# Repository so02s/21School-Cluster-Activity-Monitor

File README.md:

# 21School-Cluster-Activity-Monitor
### Description
In order to visualize clusters computers accesibility for students and make finding a coding place for oneself easier, School 21's Lab Manager Freimor (Ricky in School 21) came up with the idea of autonomous Cluster Activity Monitor.
It should be set up on each of the School's floors. We've managed to set it up on the 2nd floor.
Monitor has a map embedded in its graphics. It lights up LEDs, showing which Mac seats are occupied, which are free to use and other types of seat status. It's connected to a local network and pulls data from the metrics data-point server. 
* Monitor shows seats that are either taken, free, covid-free or used for exam.
* It also lights up the viewer's position on the map.
* Brightness of the LED is dependant on ambient light level, due to embedded light sensor.
* It should potentially support extra add-ons.

### Monitor consists of:
* 5 front PCB's which we call "modules", with school claster names (Atrium, Illusion, Oasis, Atlantis and Mirage)
  * ~450 SK9822 2020 leds
  * STM32F030* microcontroller
* 1 "motherboard" PCB
  * Raspberry Pi Zero W
  * ADS1115 for photoresistor
* Mean Well IRM-60-5ST power supply
* 3D printed skeleton structure
  * M1.2 inserted nuts and bolts for fixing modules in 3d printed front layer
  * M4 inserted nuts and bolts for fixing front layer to skeleton main body
  * 4 wall plug for fixing main body to wall
* Front PCB's shield made of polycarbonate sheet

<details><summary>Photos</summary>

</details>

Done by team: Ricky, Bomanyte.

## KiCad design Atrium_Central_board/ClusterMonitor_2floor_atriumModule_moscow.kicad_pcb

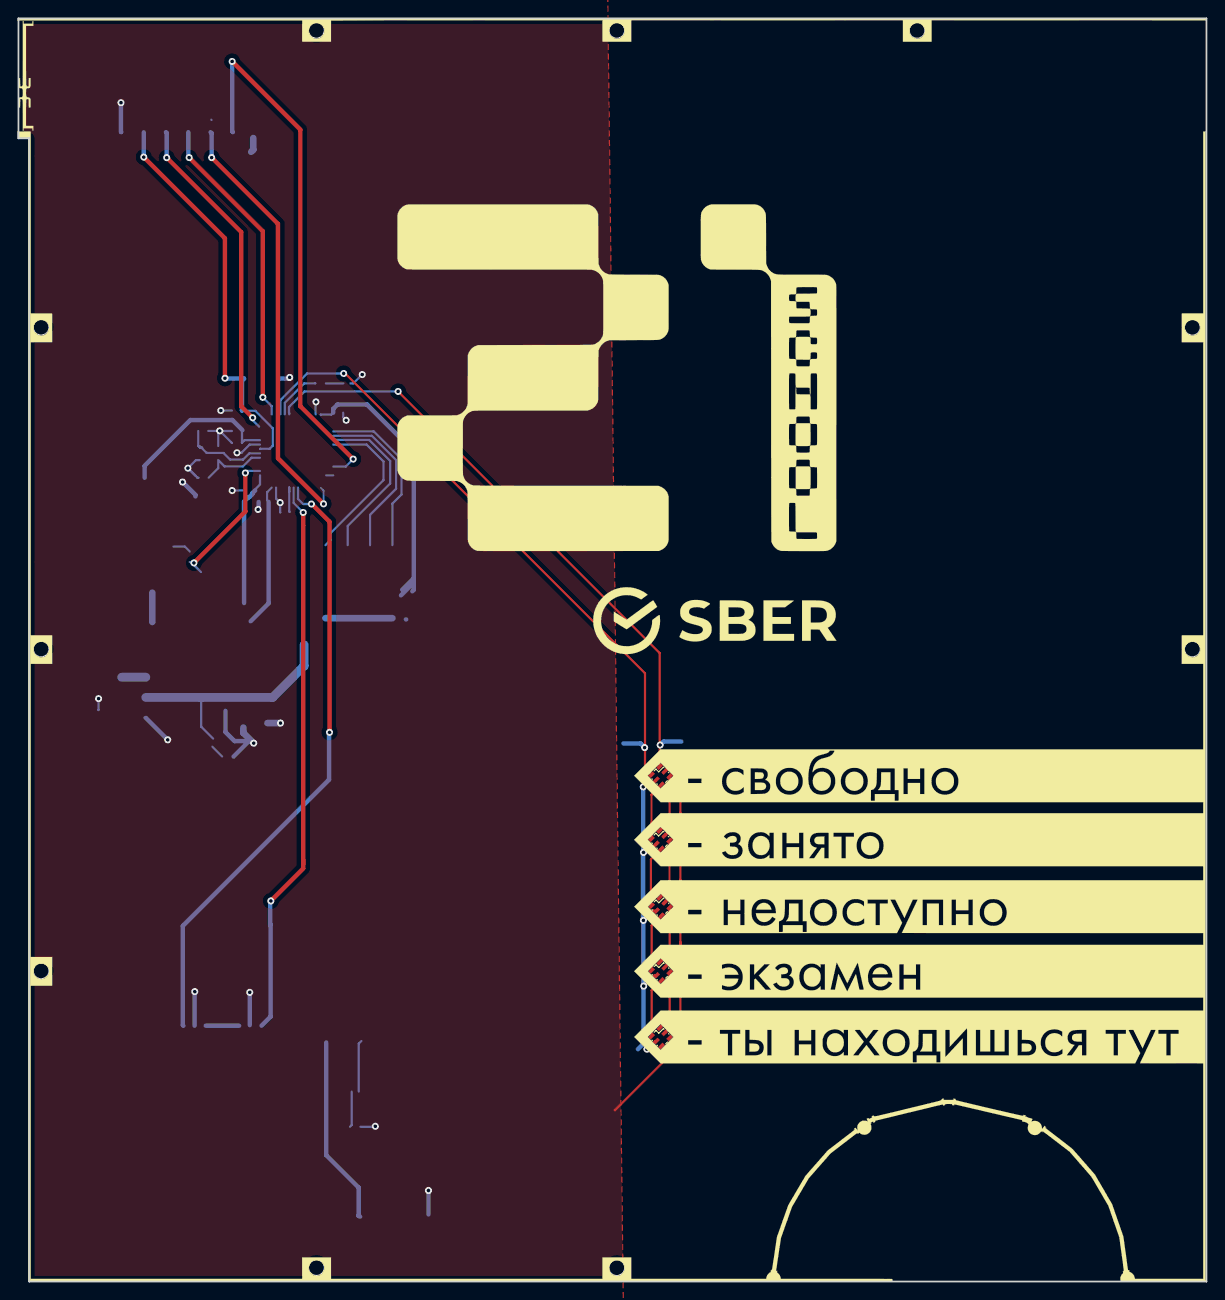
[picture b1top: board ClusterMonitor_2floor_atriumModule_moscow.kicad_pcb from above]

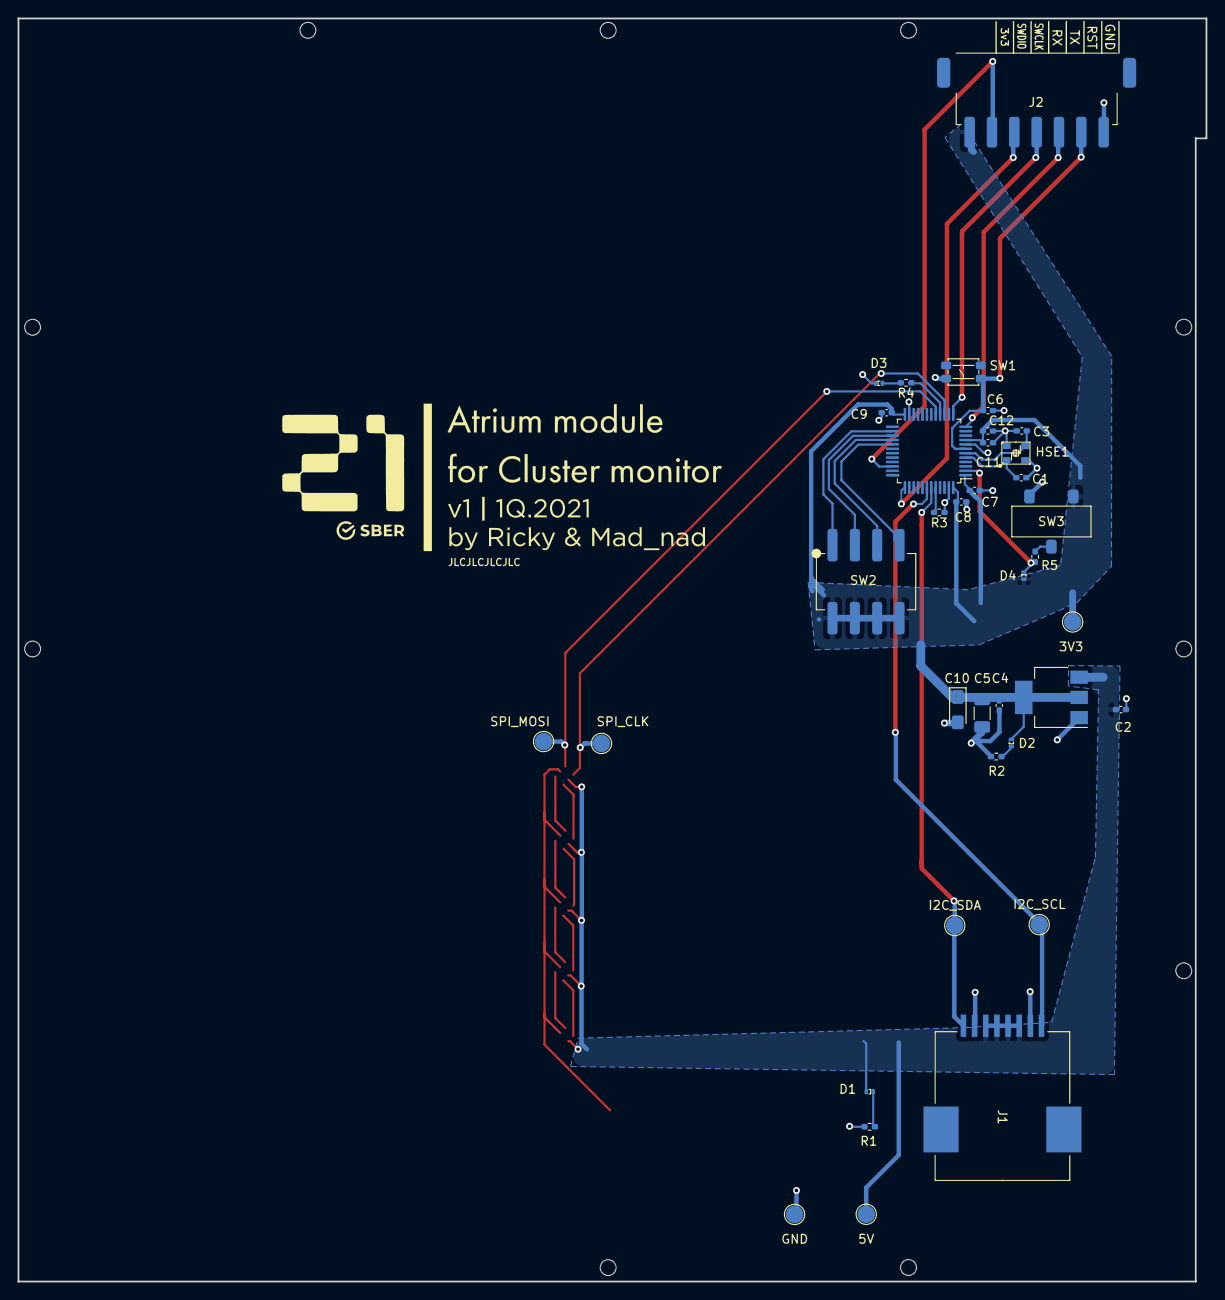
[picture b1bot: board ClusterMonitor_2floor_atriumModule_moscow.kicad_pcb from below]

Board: 2 copper layers, 135.1 x 143.6 mm, 41 parts (36 on the bottom side), 33 nets.

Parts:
3V3: TEST2; Pad_test
5V: TEST1; Pad_test
C1, C3: 15pF; C_0402_1005Metric_Pad0.74x0.62mm_HandSolder
C2, C4: 10uF; C_0402_1005Metric_Pad0.74x0.62mm_HandSolder
C5: 22uF tantal; C_1206_3216Metric_Pad1.33x1.80mm_HandSolder
C6: 0.1uF; C_0402_1005Metric_Pad0.74x0.62mm_HandSolder
C7, C8, C9: 100nF; C_0402_1005Metric_Pad0.74x0.62mm_HandSolder
C10: 4.7uF; CP_EIA-3216-10_Kemet-I_Pad1.58x1.35mm_HandSolder
C11: 10nF; C_0402_1005Metric_Pad0.74x0.62mm_HandSolder
C12: 1uF; C_0402_1005Metric_Pad0.74x0.62mm_HandSolder
D1: LED Blue (5v Power ON); LED_SMD_0402
D2: LED Red (3v3 Power ON); LED_SMD_0402
D3: Orange LED; LED_SMD_0402
D4: Purple LED; LED_SMD_0402
GND: TEST3; Pad_test
HSE1: Crystal_gnd24; ResonatorSMD_4pin(2,4GND)_KDS_1C232000AA0B
I2C_SCL: TEST4; Pad_test
I2C_SDA: TEST5; Pad_test
J1: RJ32_Shielded; rj45_molex_smd_44144-0003
J2: Conn_01x07; connector_7pin_xh2.54__lcsc_c146123_
LED1, LED2, LED3, LED4, LED5: SK9822-EC20
R1, R2, R4, R5: 1k5; R_0402_1005Metric_Pad0.72x0.64mm_HandSolder
R3: 10k; R_0402_1005Metric_Pad0.72x0.64mm_HandSolder
SPI_CLK: TEST6; Pad_test
SPI_MOSI: TEST7; Pad_test
SW1: SW_SPST; SW_SMD_XKB_(TS-1809SM-C)
SW2: ADDRESS_SELECT; SW_4poles_(LCSC_C3693)
SW3: SW_SPDT; SW_SMD_XKB_(SS-3235D-03-L1)
U1: AMS1117-3.3; SOT-223-3_TabPin2
U2: STM32F030C8Tx; LQFP-48_7x7mm_P0.5mm

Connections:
+5V: 5V.1, C2.1, D1.2, J1.3, J1.4, J1.5, J1.6, LED1.5, LED2.5, LED3.5, LED4.5, LED5.5, U1.3
C_RST: C6.2, J2.6, SW1.1, U2.7
GND: C1.2, C2.2, C3.2, C4.2, C5.2, C6.1, C7.2, C8.2, C9.2, C10.2, C11.2, C12.1, D3.1, GND.1, HSE1.2, HSE1.4, J1.2, J1.7, J2.7, LED1.2, LED2.2, LED3.2, LED4.2, LED5.2, R1.2, R2.2, R3.1, SW1.2, SW3.3, U1.1, U2.8, U2.23, U2.47
HSE_IN: C1.1, HSE1.1, U2.5
HSE_OUT: C3.1, HSE1.3, U2.6
I2C1_SCL: I2C_SCL.1, J1.8, U2.42
I2C1_SDA: I2C_SDA.1, J1.1, U2.43
unnamed: D1.1, R1.1
unnamed: D2.1, R2.1
unnamed: D3.2, R4.2
unnamed: LED1.1, LED2.3
unnamed: LED1.6, LED2.4
unnamed: LED2.1, LED3.3
unnamed: LED2.6, LED3.4
unnamed: LED3.1, LED4.3
unnamed: LED3.6, LED4.4
unnamed: LED4.1, LED5.3
unnamed: LED4.6, LED5.4
unnamed: R3.2, U2.44
unnamed: R4.1, U2.16
unnamed: R5.2, SW3.2
REG_1b: SW2.1, U2.26
REG_2b: SW2.2, U2.27
REG_3b: SW2.3, U2.28
REG_4b: SW2.4, U2.29
SPI1_CLK: LED1.4, SPI_CLK.1, U2.15
SPI1_MOSI: LED1.3, SPI_MOSI.1, U2.17
SWITCH_MODE: D4.1, R5.1, U2.2
SYS_JTCK-SWCLK: J2.3, U2.37
SYS_JTMS-SWDIO: J2.2, U2.34
USART2_RX: J2.4, U2.13
USART2_TX: J2.5, U2.12
VDDA: 3V3.1, C4.1, C5.1, C7.1, C8.1, C9.1, C10.1, C11.1, C12.2, D2.2, D4.2, J2.1, SW2.5, SW2.6, SW2.7, SW2.8, SW3.1, U1.2, U2.1, U2.9, U2.24, U2.48

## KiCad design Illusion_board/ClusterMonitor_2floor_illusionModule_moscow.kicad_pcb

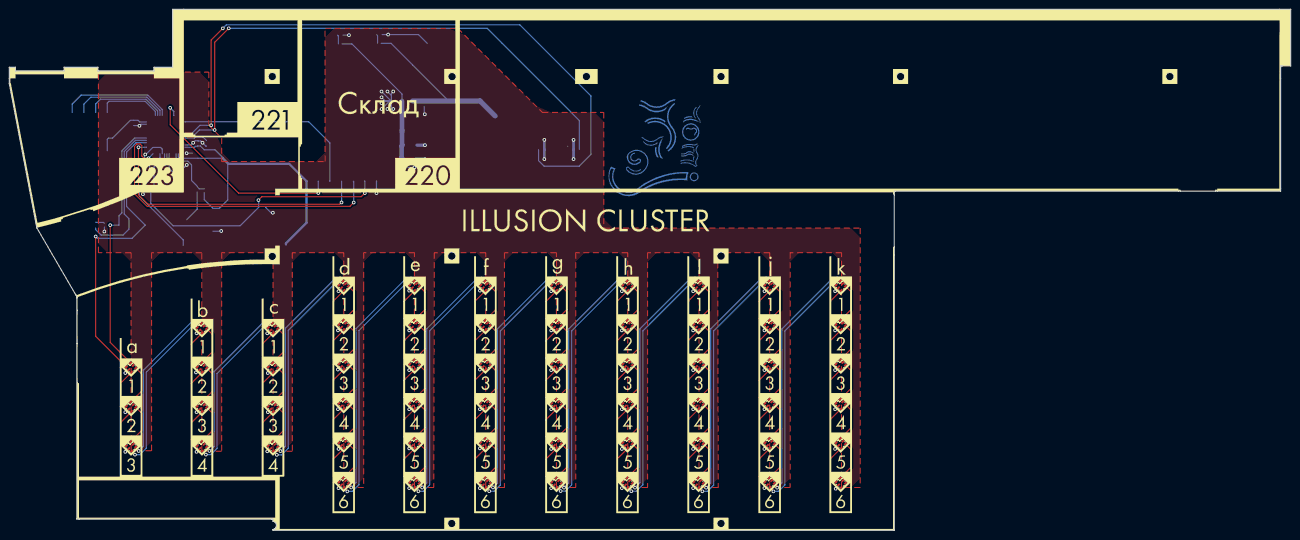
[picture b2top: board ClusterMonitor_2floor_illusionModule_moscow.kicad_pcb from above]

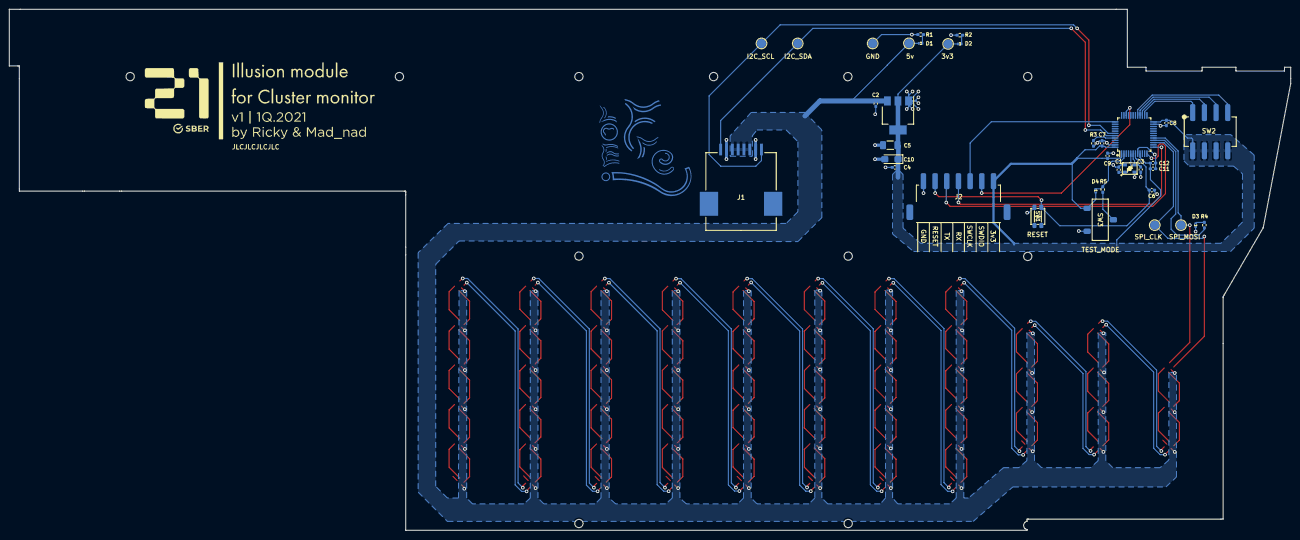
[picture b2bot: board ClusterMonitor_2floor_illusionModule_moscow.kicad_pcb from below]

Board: 2 copper layers, 278.6 x 113.3 mm, 95 parts (36 on the bottom side), 141 nets.

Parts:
C1, C3: 15pF; C_0402_1005Metric_Pad0.74x0.62mm_HandSolder
C2, C4: 10uF; C_0402_1005Metric_Pad0.74x0.62mm_HandSolder
C5: 22uF tantal; C_1206_3216Metric_Pad1.33x1.80mm_HandSolder
C6: 0.1uF; C_0402_1005Metric_Pad0.74x0.62mm_HandSolder
C7, C8, C9: 100nF; C_0402_1005Metric_Pad0.74x0.62mm_HandSolder
C10: 4.7uF; CP_EIA-3216-10_Kemet-I_Pad1.58x1.35mm_HandSolder
C11: 10nF; C_0402_1005Metric_Pad0.74x0.62mm_HandSolder
C12: 1uF; C_0402_1005Metric_Pad0.74x0.62mm_HandSolder
D1: LED Blue (5v Power ON); LED_SMD_0402
D2: LED Red (3v3 Power ON); LED_SMD_0402
D3: Orange LED; LED_SMD_0402
D4: Purple LED; LED_SMD_0402
HSE1: Crystal_gnd24; ResonatorSMD_4pin(2,4GND)_KDS_1C232000AA0B
J1: RJ45_Molex_smd_44144-0003
J2: Conn_01x07; Connector_7pin_XH2.54_(LCSC_C146123)
LED-a-1, LED-a-2, LED-a-3: SK9822-EC20
LED-b-1, LED-b-2, LED-b-3, LED-b-4: SK9822-EC20
LED-c-1, LED-c-2, LED-c-3, LED-c-4: SK9822-EC20
LED-d-1, LED-d-3, LED-d-4, LED-d-5, LED-d-6: SK9822-EC20
LED-d-e: SK9822-EC20
LED-e-1, LED-e-2, LED-e-3, LED-e-4, LED-e-5, LED-e-6: SK9822-EC20
LED-f-1, LED-f-2, LED-f-3, LED-f-4, LED-f-5, LED-f-6: SK9822-EC20
LED-g-1, LED-g-2, LED-g-3, LED-g-4, LED-g-5, LED-g-6: SK9822-EC20
LED-h-1, LED-h-2, LED-h-3, LED-h-4, LED-h-5, LED-h-6: SK9822-EC20
LED-i-1, LED-i-2, LED-i-3, LED-i-4, LED-i-5, LED-i-6: SK9822-EC20
LED-j-1, LED-j-2, LED-j-3, LED-j-4, LED-j-5, LED-j-6: SK9822-EC20
LED-k-1, LED-k-2, LED-k-3, LED-k-4, LED-k-5, LED-k-6: SK9822-EC20
R1, R2, R4, R5: 1k5; R_0402_1005Metric_Pad0.72x0.64mm_HandSolder
R3: 10k; R_0402_1005Metric_Pad0.72x0.64mm_HandSolder
SW1: SW_SPST_Double; SW_SMD_XKB_(TS-1809SM-C)
SW2: ADDRESS_SELECT; SW_4poles_(LCSC_C3693)
SW3: SW_SPDT; SW_SMD_XKB_(SS-3235D-03-L1)
TEST1, TEST2, TEST3, TEST4, TEST5, TEST6, TEST7: test_pad_circle2mm; Pad_test
U1: AMS1117-3.3; SOT-223-3_TabPin2
U2: STM32F030C8Tx; LQFP-48_7x7mm_P0.5mm

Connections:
+5V: C2.1, D1.2, J1.3, J1.4, J1.5, J1.6, LED-a-1.5, LED-a-2.5, LED-a-3.5, LED-b-1.5, LED-b-2.5, LED-b-3.5, LED-b-4.5, LED-c-1.5, LED-c-2.5, LED-c-3.5, LED-c-4.5, LED-d-1.5, LED-d-3.5, LED-d-4.5, LED-d-5.5, LED-d-6.5, LED-d-e.5, LED-e-1.5, LED-e-2.5, LED-e-3.5, LED-e-4.5, LED-e-5.5, LED-e-6.5, LED-f-1.5, LED-f-2.5, LED-f-3.5, LED-f-4.5, LED-f-5.5, LED-f-6.5, LED-g-1.5, LED-g-2.5, LED-g-3.5, LED-g-4.5, LED-g-5.5, LED-g-6.5, LED-h-1.5, LED-h-2.5, LED-h-3.5, LED-h-4.5, LED-h-5.5, LED-h-6.5, LED-i-1.5, LED-i-2.5, LED-i-3.5, LED-i-4.5, LED-i-5.5, LED-i-6.5, LED-j-1.5, LED-j-2.5, LED-j-3.5, LED-j-4.5, LED-j-5.5, LED-j-6.5, LED-k-1.5, LED-k-2.5, LED-k-3.5, LED-k-4.5, LED-k-5.5, LED-k-6.5, TEST1.1, U1.3
C_RST: C6.2, J2.6, SW1.1, U2.7
GND: C1.2, C2.2, C3.2, C4.2, C5.2, C6.1, C7.2, C8.2, C9.2, C10.2, C11.2, C12.1, D3.1, HSE1.2, HSE1.4, J1.2, J1.7, J2.7, LED-a-1.2, LED-a-2.2, LED-a-3.2, LED-b-1.2, LED-b-2.2, LED-b-3.2, LED-b-4.2, LED-c-1.2, LED-c-2.2, LED-c-3.2, LED-c-4.2, LED-d-1.2, LED-d-3.2, LED-d-4.2, LED-d-5.2, LED-d-6.2, LED-d-e.2, LED-e-1.2, LED-e-2.2, LED-e-3.2, LED-e-4.2, LED-e-5.2, LED-e-6.2, LED-f-1.2, LED-f-2.2, LED-f-3.2, LED-f-4.2, LED-f-5.2, LED-f-6.2, LED-g-1.2, LED-g-2.2, LED-g-3.2, LED-g-4.2, LED-g-5.2, LED-g-6.2, LED-h-1.2, LED-h-2.2, LED-h-3.2, LED-h-4.2, LED-h-5.2, LED-h-6.2, LED-i-1.2, LED-i-2.2, LED-i-3.2, LED-i-4.2, LED-i-5.2, LED-i-6.2, LED-j-1.2, LED-j-2.2, LED-j-3.2, LED-j-4.2, LED-j-5.2, LED-j-6.2, LED-k-1.2, LED-k-2.2, LED-k-3.2, LED-k-4.2, LED-k-5.2, LED-k-6.2, R1.2, R2.2, R3.1, SW1.3, SW3.3, TEST3.1, U1.1, U2.8, U2.23, U2.47
HSE_IN: C1.1, HSE1.1, U2.5
HSE_OUT: C3.1, HSE1.3, U2.6
I2C2_SCL: J1.8, TEST4.1, U2.42
I2C2_SDA: J1.1, TEST5.1, U2.43
unnamed: D1.1, R1.1
unnamed: D2.1, R2.1
unnamed: D3.2, R4.2
unnamed: LED-a-1.1, LED-a-2.3
unnamed: LED-a-1.6, LED-a-2.4
unnamed: LED-a-2.1, LED-a-3.3
unnamed: LED-a-2.6, LED-a-3.4
unnamed: LED-a-3.1, LED-b-1.3
unnamed: LED-a-3.6, LED-b-1.4
unnamed: LED-b-1.1, LED-b-2.3
unnamed: LED-b-1.6, LED-b-2.4
unnamed: LED-b-2.1, LED-b-3.3
unnamed: LED-b-2.6, LED-b-3.4
unnamed: LED-b-3.1, LED-b-4.3
unnamed: LED-b-3.6, LED-b-4.4
unnamed: LED-b-4.1, LED-c-1.3
unnamed: LED-b-4.6, LED-c-1.4
unnamed: LED-c-1.1, LED-c-2.3
unnamed: LED-c-1.6, LED-c-2.4
unnamed: LED-c-2.1, LED-c-3.3
unnamed: LED-c-2.6, LED-c-3.4
unnamed: LED-c-3.1, LED-c-4.3
unnamed: LED-c-3.6, LED-c-4.4
unnamed: LED-c-4.1, LED-d-1.3
unnamed: LED-c-4.6, LED-d-1.4
unnamed: LED-d-1.1, LED-d-e.3
unnamed: LED-d-1.6, LED-d-e.4
unnamed: LED-d-3.3, LED-d-e.1
unnamed: LED-d-3.4, LED-d-e.6
unnamed: LED-d-3.1, LED-d-4.3
unnamed: LED-d-3.6, LED-d-4.4
unnamed: LED-d-4.1, LED-d-5.3
unnamed: LED-d-4.6, LED-d-5.4
unnamed: LED-d-5.1, LED-d-6.3
unnamed: LED-d-5.6, LED-d-6.4
unnamed: LED-d-6.1, LED-e-1.3
unnamed: LED-d-6.6, LED-e-1.4
unnamed: LED-e-1.1, LED-e-2.3
unnamed: LED-e-1.6, LED-e-2.4
unnamed: LED-e-2.1, LED-e-3.3
unnamed: LED-e-2.6, LED-e-3.4
unnamed: LED-e-3.1, LED-e-4.3
unnamed: LED-e-3.6, LED-e-4.4
unnamed: LED-e-4.1, LED-e-5.3
unnamed: LED-e-4.6, LED-e-5.4
unnamed: LED-e-5.1, LED-e-6.3
unnamed: LED-e-5.6, LED-e-6.4
unnamed: LED-e-6.1, LED-f-1.3
unnamed: LED-e-6.6, LED-f-1.4
unnamed: LED-f-1.1, LED-f-2.3
unnamed: LED-f-1.6, LED-f-2.4
unnamed: LED-f-2.1, LED-f-3.3
unnamed: LED-f-2.6, LED-f-3.4
unnamed: LED-f-3.1, LED-f-4.3
unnamed: LED-f-3.6, LED-f-4.4
unnamed: LED-f-4.1, LED-f-5.3
unnamed: LED-f-4.6, LED-f-5.4
unnamed: LED-f-5.1, LED-f-6.3
unnamed: LED-f-5.6, LED-f-6.4
unnamed: LED-f-6.1, LED-g-1.3
unnamed: LED-f-6.6, LED-g-1.4
unnamed: LED-g-1.1, LED-g-2.3
unnamed: LED-g-1.6, LED-g-2.4
unnamed: LED-g-2.1, LED-g-3.3
unnamed: LED-g-2.6, LED-g-3.4
unnamed: LED-g-3.1, LED-g-4.3
unnamed: LED-g-3.6, LED-g-4.4
unnamed: LED-g-4.1, LED-g-5.3
unnamed: LED-g-4.6, LED-g-5.4
unnamed: LED-g-5.1, LED-g-6.3
unnamed: LED-g-5.6, LED-g-6.4
unnamed: LED-g-6.1, LED-h-1.3
unnamed: LED-g-6.6, LED-h-1.4
unnamed: LED-h-1.1, LED-h-2.3
unnamed: LED-h-1.6, LED-h-2.4
unnamed: LED-h-2.1, LED-h-3.3
unnamed: LED-h-2.6, LED-h-3.4
unnamed: LED-h-3.1, LED-h-4.3
unnamed: LED-h-3.6, LED-h-4.4
unnamed: LED-h-4.1, LED-h-5.3
unnamed: LED-h-4.6, LED-h-5.4
unnamed: LED-h-5.1, LED-h-6.3
unnamed: LED-h-5.6, LED-h-6.4
unnamed: LED-h-6.1, LED-i-1.3
unnamed: LED-h-6.6, LED-i-1.4
unnamed: LED-i-1.1, LED-i-2.3
unnamed: LED-i-1.6, LED-i-2.4
unnamed: LED-i-2.1, LED-i-3.3
unnamed: LED-i-2.6, LED-i-3.4
unnamed: LED-i-3.1, LED-i-4.3
unnamed: LED-i-3.6, LED-i-4.4
unnamed: LED-i-4.1, LED-i-5.3
unnamed: LED-i-4.6, LED-i-5.4
unnamed: LED-i-5.1, LED-i-6.3
unnamed: LED-i-5.6, LED-i-6.4
unnamed: LED-i-6.1, LED-j-1.3
unnamed: LED-i-6.6, LED-j-1.4
unnamed: LED-j-1.1, LED-j-2.3
unnamed: LED-j-1.6, LED-j-2.4
unnamed: LED-j-2.1, LED-j-3.3
unnamed: LED-j-2.6, LED-j-3.4
unnamed: LED-j-3.1, LED-j-4.3
unnamed: LED-j-3.6, LED-j-4.4
unnamed: LED-j-4.1, LED-j-5.3
unnamed: LED-j-4.6, LED-j-5.4
unnamed: LED-j-5.1, LED-j-6.3
unnamed: LED-j-5.6, LED-j-6.4
unnamed: LED-j-6.1, LED-k-1.3
unnamed: LED-j-6.6, LED-k-1.4
unnamed: LED-k-1.1, LED-k-2.3
unnamed: LED-k-1.6, LED-k-2.4
unnamed: LED-k-2.1, LED-k-3.3
unnamed: LED-k-2.6, LED-k-3.4
unnamed: LED-k-3.1, LED-k-4.3
unnamed: LED-k-3.6, LED-k-4.4
unnamed: LED-k-4.1, LED-k-5.3
unnamed: LED-k-4.6, LED-k-5.4
unnamed: LED-k-5.1, LED-k-6.3
unnamed: LED-k-5.6, LED-k-6.4
unnamed: R3.2, U2.44
unnamed: R4.1, U2.16
unnamed: R5.2, SW3.2
REG_1b: SW2.1, U2.26
REG_2b: SW2.2, U2.27
REG_3b: SW2.3, U2.28
REG_4b: SW2.4, U2.29
SPI1_CLK: LED-a-1.4, TEST6.1, U2.15
SPI1_MOSI: LED-a-1.3, TEST7.1, U2.17
SWITCH_MODE: D4.1, R5.1, U2.2
SYS_JTCK-SWCLK: J2.3, U2.37
SYS_JTMS-SWDIO: J2.2, U2.34
USART2_RX: J2.4, U2.13
USART2_TX: J2.5, U2.12
VDDA: C4.1, C5.1, C7.1, C8.1, C9.1, C10.1, C11.1, C12.2, D2.2, D4.2, J2.1, SW2.5, SW2.6, SW2.7, SW2.8, SW3.1, TEST2.1, U1.2, U2.1, U2.9, U2.24, U2.48

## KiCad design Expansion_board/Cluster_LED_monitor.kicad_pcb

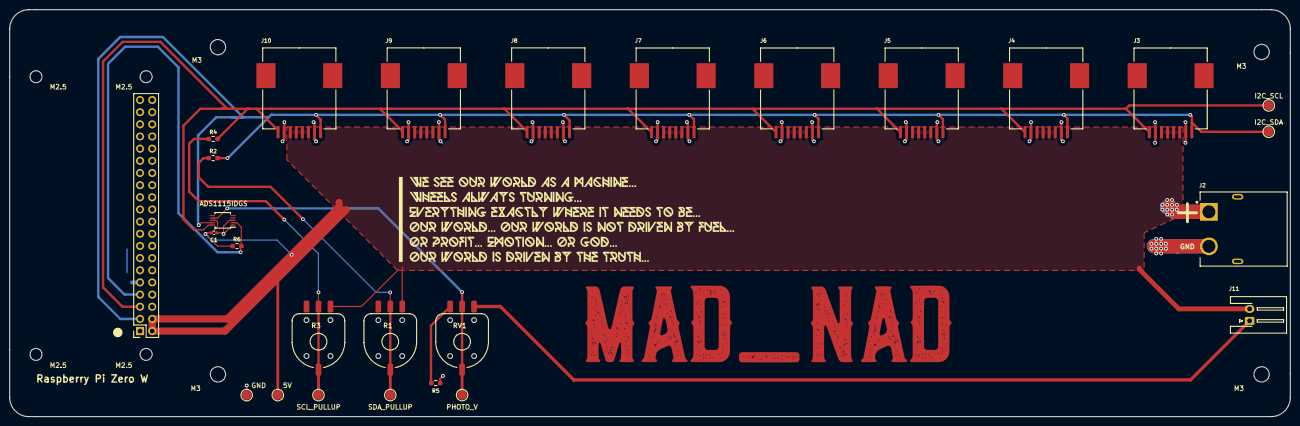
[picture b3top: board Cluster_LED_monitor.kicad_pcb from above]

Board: 2 copper layers, 267.5 x 85.0 mm, 27 parts (0 on the bottom side), 10 nets.

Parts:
5V: TestPoint_Pad_D2.0mm
C1: 0.1uF; C_0402_1005Metric_Pad0.74x0.62mm_HandSolder
GND: TestPoint_Pad_D2.0mm
I2C_SCL, I2C_SDA: TestPoint_Pad_D2.0mm
J1: Raspberry_Pi_2_3; PinSocket_2x20_P2.54mm_Vertical
J2: Conn_01x02_Female; AMASS_XT60PW-M
J3, J4, J5, J6, J7, J8, J9, J10: RJ45; rj45_molex_smd_44144-0003
J11: Conn_01x02; JST_XH_S2B-XH-A-1_1x02_P2.50mm_Horizontal
PHOTO_V: TestPoint_Pad_D2.0mm
R1, R3: R_Variable; _var_res_RDC503013A
R2, R4, R5: 680; R_0603_1608Metric_Pad0.98x0.95mm_HandSolder
R6: 5K1; R_0603_1608Metric_Pad0.98x0.95mm_HandSolder
RV1: R_POT; _var_res_RDC503013A
SCL_PULLUP: TestPoint_Pad_D2.0mm
SDA_PULLUP: TestPoint_Pad_D2.0mm
U1: ADS1115IDGS; TSSOP-10_3x3mm_P0.5mm

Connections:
+5V: 5V.1, C1.1, J1.2, J1.4, J2.1, J3.3, J3.4, J3.5, J3.6, J4.3, J4.4, J4.5, J4.6, J5.3, J5.4, J5.5, J5.6, J6.3, J6.4, J6.5, J6.6, J7.3, J7.4, J7.5, J7.6, J8.3, J8.4, J8.5, J8.6, J9.3, J9.4, J9.5, J9.6, J10.3, J10.4, J10.5, J10.6, J11.2, R1.1, R3.1, R6.1, U1.8
GND: C1.2, GND.1, J1.6, J1.9, J1.14, J1.20, J1.25, J1.30, J1.34, J1.39, J2.2, J3.2, J3.7, J4.2, J4.7, J5.2, J5.7, J6.2, J6.7, J7.2, J7.7, J8.2, J8.7, J9.2, J9.7, J10.2, J10.7, R5.2, U1.1, U1.3
I2C_SCL: I2C_SCL.1, J1.5, J3.8, J4.8, J5.8, J6.8, J7.8, J8.8, J9.8, J10.8, R4.2, U1.10
I2C_SDA: I2C_SDA.1, J1.3, J3.1, J4.1, J5.1, J6.1, J7.1, J8.1, J9.1, J10.1, R2.2, U1.9
unnamed: J1.7, R6.2, U1.2
unnamed: J11.1, RV1.1
unnamed: R1.2, R2.1, SDA_PULLUP.1
unnamed: R3.2, R4.1, SCL_PULLUP.1
unnamed: R5.1, RV1.3
unnamed: PHOTO_V.1, RV1.2, U1.7

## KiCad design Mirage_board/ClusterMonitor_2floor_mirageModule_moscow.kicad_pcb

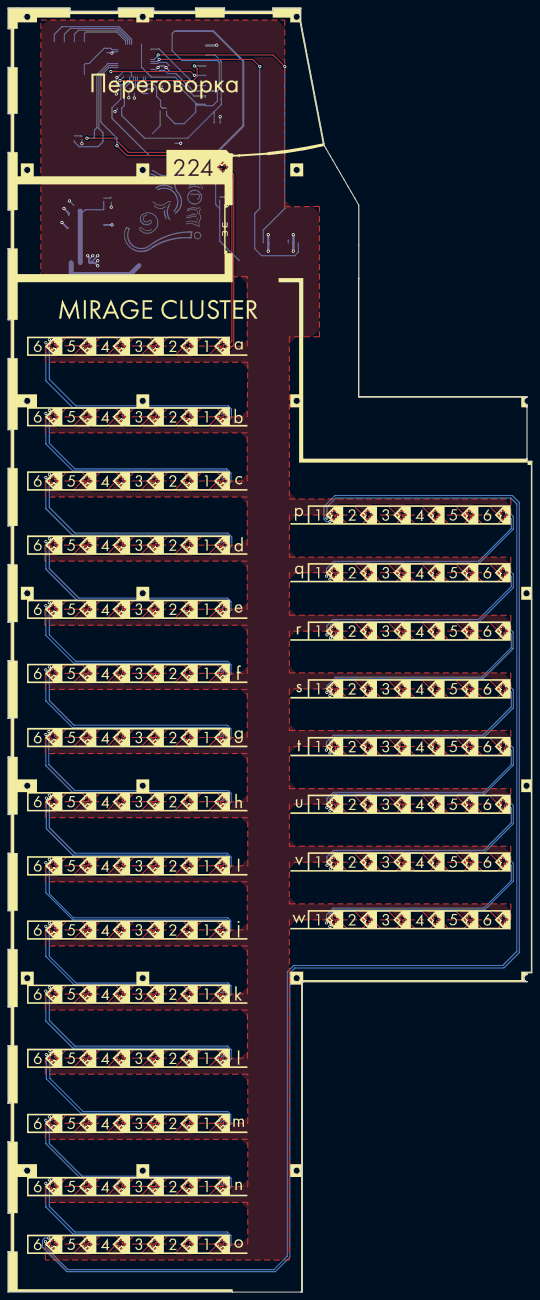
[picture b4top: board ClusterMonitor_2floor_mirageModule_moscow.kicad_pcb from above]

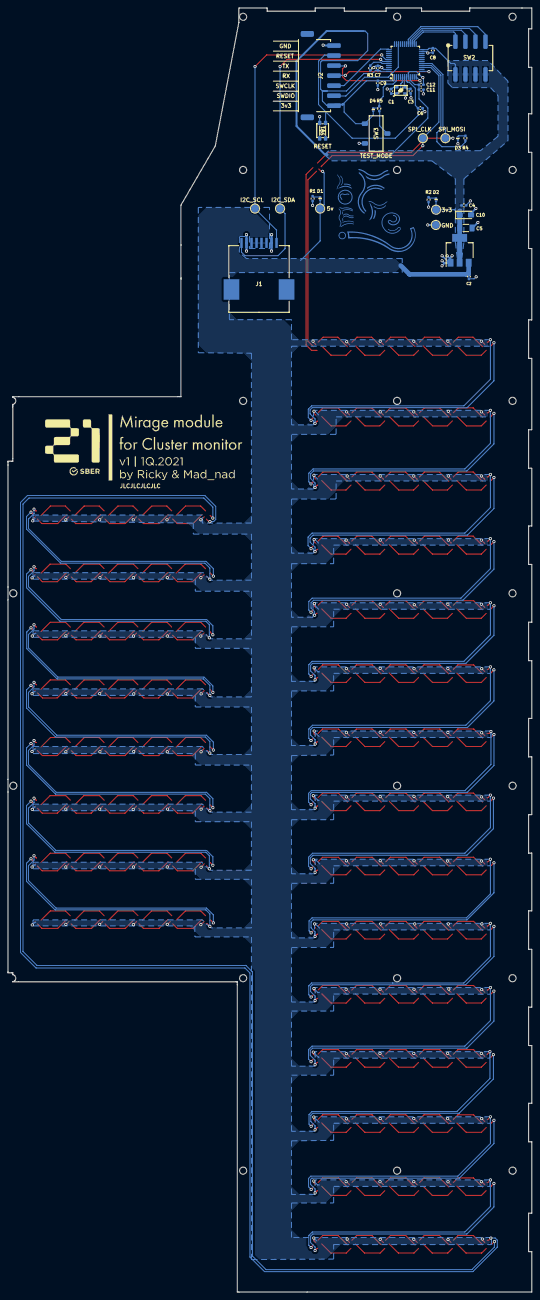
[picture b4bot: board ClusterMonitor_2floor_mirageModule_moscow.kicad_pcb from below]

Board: 2 copper layers, 132.8 x 325.5 mm, 175 parts (36 on the bottom side), 301 nets.

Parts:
C1, C3: 15pF; C_0402_1005Metric_Pad0.74x0.62mm_HandSolder
C2, C4: 10uF; C_0402_1005Metric_Pad0.74x0.62mm_HandSolder
C5: 22uF tantal; C_1206_3216Metric_Pad1.33x1.80mm_HandSolder
C6: 0.1uF; C_0402_1005Metric_Pad0.74x0.62mm_HandSolder
C7, C8, C9: 100nF; C_0402_1005Metric_Pad0.74x0.62mm_HandSolder
C10: 4.7uF; CP_EIA-3216-10_Kemet-I_Pad1.58x1.35mm_HandSolder
C11: 10nF; C_0402_1005Metric_Pad0.74x0.62mm_HandSolder
C12: 1uF; C_0402_1005Metric_Pad0.74x0.62mm_HandSolder
D1: LED Blue (5v Power ON); LED_SMD_0402
D2: LED Red (3v3 Power ON); LED_SMD_0402
D3: Orange LED; LED_SMD_0402
D4: Purple LED; LED_SMD_0402
HSE1: Crystal_gnd24; ResonatorSMD_4pin(2,4GND)_KDS_1C232000AA0B
J1: RJ45_Molex_smd_44144-0003
J2: Conn_01x07; Connector_7pin_XH2.54_(LCSC_C146123)
LED-a-1, LED-a-2, LED-a-3, LED-a-4, LED-a-5, LED-a-6: SK9822-EC20
LED-b-1, LED-b-2, LED-b-3, LED-b-4, LED-b-5, LED-b-6: SK9822-EC20
LED-c-1, LED-c-2, LED-c-3, LED-c-4, LED-c-5, LED-c-6: SK9822-EC20
LED-d-1, LED-d-2, LED-d-3, LED-d-4, LED-d-5, LED-d-6: SK9822-EC20
LED-e-1, LED-e-2, LED-e-3, LED-e-4, LED-e-5, LED-e-6: SK9822-EC20
LED-f-1, LED-f-2, LED-f-3, LED-f-4, LED-f-5, LED-f-6: SK9822-EC20
LED-g-1, LED-g-2, LED-g-3, LED-g-4, LED-g-5, LED-g-6: SK9822-EC20
LED-h-1, LED-h-2, LED-h-3, LED-h-4, LED-h-5, LED-h-6: SK9822-EC20
LED-i-1, LED-i-2, LED-i-3, LED-i-4, LED-i-5, LED-i-6: SK9822-EC20
LED-j-1, LED-j-2, LED-j-3, LED-j-4, LED-j-5, LED-j-6: SK9822-EC20
LED-k-1, LED-k-2, LED-k-3, LED-k-4, LED-k-5, LED-k-6: SK9822-EC20
LED-l-1, LED-l-2, LED-l-3, LED-l-4, LED-l-5, LED-l-6: SK9822-EC20
LED-m-1, LED-m-2, LED-m-3, LED-m-4, LED-m-5, LED-m-6: SK9822-EC20
LED-n-1, LED-n-2, LED-n-3, LED-n-4, LED-n-5, LED-n-6: SK9822-EC20
LED-o-1, LED-o-2, LED-o-3, LED-o-4, LED-o-5, LED-o-6: SK9822-EC20
LED-p-1, LED-p-2, LED-p-3, LED-p-4, LED-p-5, LED-p-6: SK9822-EC20
LED-peregov-0: SK9822-EC20
LED-q-1, LED-q-2, LED-q-3, LED-q-4, LED-q-5, LED-q-6: SK9822-EC20
LED-r-1, LED-r-2, LED-r-3, LED-r-4, LED-r-5, LED-r-6: SK9822-EC20
LED-s-1, LED-s-2, LED-s-3, LED-s-4, LED-s-5, LED-s-6: SK9822-EC20
LED-t-1, LED-t-2, LED-t-3, LED-t-4, LED-t-5, LED-t-6: SK9822-EC20
LED-u-1, LED-u-2, LED-u-3, LED-u-4, LED-u-5, LED-u-6: SK9822-EC20
LED-v-1, LED-v-2, LED-v-3, LED-v-4, LED-v-5, LED-v-6: SK9822-EC20
LED-w-1, LED-w-2, LED-w-3, LED-w-4, LED-w-5, LED-w-6: SK9822-EC20
R1, R2, R4, R5: 1k5; R_0402_1005Metric_Pad0.72x0.64mm_HandSolder
R3: 10k; R_0402_1005Metric_Pad0.72x0.64mm_HandSolder
SW1: SW_SPST_Double; SW_SMD_XKB_(TS-1809SM-C)
SW2: ADDRESS_SELECT; SW_4poles_(LCSC_C3693)
SW3: SW_SPDT; SW_SMD_XKB_(SS-3235D-03-L1)
TEST1, TEST2, TEST3, TEST4, TEST5, TEST6, TEST7: test_pad_circle2mm; Pad_test
U1: AMS1117-3.3; SOT-223-3_TabPin2
U2: STM32F030C8Tx; LQFP-48_7x7mm_P0.5mm

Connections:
+5V: C2.1, D1.2, J1.3, J1.4, J1.5, J1.6, LED-a-1.5, LED-a-2.5, LED-a-3.5, LED-a-4.5, LED-a-5.5, LED-a-6.5, LED-b-1.5, LED-b-2.5, LED-b-3.5, LED-b-4.5, LED-b-5.5, LED-b-6.5, LED-c-1.5, LED-c-2.5, LED-c-3.5, LED-c-4.5, LED-c-5.5, LED-c-6.5, LED-d-1.5, LED-d-2.5, LED-d-3.5, LED-d-4.5, LED-d-5.5, LED-d-6.5, LED-e-1.5, LED-e-2.5, LED-e-3.5, LED-e-4.5, LED-e-5.5, LED-e-6.5, LED-f-1.5, LED-f-2.5, LED-f-3.5, LED-f-4.5, LED-f-5.5, LED-f-6.5, LED-g-1.5, LED-g-2.5, LED-g-3.5, LED-g-4.5, LED-g-5.5, LED-g-6.5, LED-h-1.5, LED-h-2.5, LED-h-3.5, LED-h-4.5, LED-h-5.5, LED-h-6.5, LED-i-1.5, LED-i-2.5, LED-i-3.5, LED-i-4.5, LED-i-5.5, LED-i-6.5, LED-j-1.5, LED-j-2.5, LED-j-3.5, LED-j-4.5, LED-j-5.5, LED-j-6.5, LED-k-1.5, LED-k-2.5, LED-k-3.5, LED-k-4.5, LED-k-5.5, LED-k-6.5, LED-l-1.5, LED-l-2.5, LED-l-3.5, LED-l-4.5, LED-l-5.5, LED-l-6.5, LED-m-1.5, LED-m-2.5, LED-m-3.5, LED-m-4.5, LED-m-5.5, LED-m-6.5, LED-n-1.5, LED-n-2.5, LED-n-3.5, LED-n-4.5, LED-n-5.5, LED-n-6.5, LED-o-1.5, LED-o-2.5, LED-o-3.5, LED-o-4.5, LED-o-5.5, LED-o-6.5, LED-p-1.5, LED-p-2.5, LED-p-3.5, LED-p-4.5, LED-p-5.5, LED-p-6.5, LED-peregov-0.5, LED-q-1.5, LED-q-2.5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
C_RST: C6.2, J2.6, SW1.1, U2.7
GND: C1.2, C2.2, C3.2, C4.2, C5.2, C6.1, C7.2, C8.2, C9.2, C10.2, C11.2, C12.1, D3.1, HSE1.2, HSE1.4, J1.2, J1.7, J2.7, LED-a-1.2, LED-a-2.2, LED-a-3.2, LED-a-4.2, LED-a-5.2, LED-a-6.2, LED-b-1.2, LED-b-2.2, LED-b-3.2, LED-b-4.2, LED-b-5.2, LED-b-6.2, LED-c-1.2, LED-c-2.2, LED-c-3.2, LED-c-4.2, LED-c-5.2, LED-c-6.2, LED-d-1.2, LED-d-2.2, LED-d-3.2, LED-d-4.2, LED-d-5.2, LED-d-6.2, LED-e-1.2, LED-e-2.2, LED-e-3.2, LED-e-4.2, LED-e-5.2, LED-e-6.2, LED-f-1.2, LED-f-2.2, LED-f-3.2, LED-f-4.2, LED-f-5.2, LED-f-6.2, LED-g-1.2, LED-g-2.2, LED-g-3.2, LED-g-4.2, LED-g-5.2, LED-g-6.2, LED-h-1.2, LED-h-2.2, LED-h-3.2, LED-h-4.2, LED-h-5.2, LED-h-6.2, LED-i-1.2, LED-i-2.2, LED-i-3.2, LED-i-4.2, LED-i-5.2, LED-i-6.2, LED-j-1.2, LED-j-2.2, LED-j-3.2, LED-j-4.2, LED-j-5.2, LED-j-6.2, LED-k-1.2, LED-k-2.2, LED-k-3.2, LED-k-4.2, LED-k-5.2, LED-k-6.2, LED-l-1.2, LED-l-2.2, LED-l-3.2, LED-l-4.2, LED-l-5.2, LED-l-6.2, LED-m-1.2, LED-m-2.2, LED-m-3.2, LED-m-4.2, LED-m-5.2, LED-m-6.2, LED-n-1.2, LED-n-2.2, LED-n-3.2, LED-n-4.2, LED-n-5.2, LED-n-6.2, LED-o-1.2, LED-o-2.2, LED-o-3.2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
HSE_IN: C1.1, HSE1.1, U2.5
HSE_OUT: C3.1, HSE1.3, U2.6
I2C2_SCL: J1.8, TEST4.1, U2.42
I2C2_SDA: J1.1, TEST5.1, U2.43
unnamed: D1.1, R1.1
unnamed: D2.1, R2.1
unnamed: D3.2, R4.2
unnamed: LED-a-1.1, LED-a-2.3
unnamed: LED-a-1.3, LED-peregov-0.1
unnamed: LED-a-1.4, LED-peregov-0.6
unnamed: LED-a-1.6, LED-a-2.4
unnamed: LED-a-2.1, LED-a-3.3
unnamed: LED-a-2.6, LED-a-3.4
unnamed: LED-a-3.1, LED-a-4.3
unnamed: LED-a-3.6, LED-a-4.4
unnamed: LED-a-4.1, LED-a-5.3
unnamed: LED-a-4.6, LED-a-5.4
unnamed: LED-a-5.1, LED-a-6.3
unnamed: LED-a-5.6, LED-a-6.4
unnamed: LED-a-6.1, LED-b-1.3
unnamed: LED-a-6.6, LED-b-1.4
unnamed: LED-b-1.1, LED-b-2.3
unnamed: LED-b-1.6, LED-b-2.4
unnamed: LED-b-2.1, LED-b-3.3
unnamed: LED-b-2.6, LED-b-3.4
unnamed: LED-b-3.1, LED-b-4.3
unnamed: LED-b-3.6, LED-b-4.4
unnamed: LED-b-4.1, LED-b-5.3
unnamed: LED-b-4.6, LED-b-5.4
unnamed: LED-b-5.1, LED-b-6.3
unnamed: LED-b-5.6, LED-b-6.4
unnamed: LED-b-6.1, LED-c-1.3
unnamed: LED-b-6.6, LED-c-1.4
unnamed: LED-c-1.1, LED-c-2.3
unnamed: LED-c-1.6, LED-c-2.4
unnamed: LED-c-2.1, LED-c-3.3
unnamed: LED-c-2.6, LED-c-3.4
unnamed: LED-c-3.1, LED-c-4.3
unnamed: LED-c-3.6, LED-c-4.4
unnamed: LED-c-4.1, LED-c-5.3
unnamed: LED-c-4.6, LED-c-5.4
unnamed: LED-c-5.1, LED-c-6.3
unnamed: LED-c-5.6, LED-c-6.4
unnamed: LED-c-6.1, LED-d-1.3
unnamed: LED-c-6.6, LED-d-1.4
unnamed: LED-d-1.1, LED-d-2.3
unnamed: LED-d-1.6, LED-d-2.4
unnamed: LED-d-2.1, LED-d-3.3
unnamed: LED-d-2.6, LED-d-3.4
unnamed: LED-d-3.1, LED-d-4.3
unnamed: LED-d-3.6, LED-d-4.4
unnamed: LED-d-4.1, LED-d-5.3
unnamed: LED-d-4.6, LED-d-5.4
unnamed: LED-d-5.1, LED-d-6.3
unnamed: LED-d-5.6, LED-d-6.4
unnamed: LED-d-6.1, LED-e-1.3
unnamed: LED-d-6.6, LED-e-1.4
unnamed: LED-e-1.1, LED-e-2.3
unnamed: LED-e-1.6, LED-e-2.4
unnamed: LED-e-2.1, LED-e-3.3
unnamed: LED-e-2.6, LED-e-3.4
unnamed: LED-e-3.1, LED-e-4.3
unnamed: LED-e-3.6, LED-e-4.4
unnamed: LED-e-4.1, LED-e-5.3
unnamed: LED-e-4.6, LED-e-5.4
unnamed: LED-e-5.1, LED-e-6.3
unnamed: LED-e-5.6, LED-e-6.4
unnamed: LED-e-6.1, LED-f-1.3
unnamed: LED-e-6.6, LED-f-1.4
unnamed: LED-f-1.1, LED-f-2.3
unnamed: LED-f-1.6, LED-f-2.4
unnamed: LED-f-2.1, LED-f-3.3
unnamed: LED-f-2.6, LED-f-3.4
unnamed: LED-f-3.1, LED-f-4.3
unnamed: LED-f-3.6, LED-f-4.4
unnamed: LED-f-4.1, LED-f-5.3
unnamed: LED-f-4.6, LED-f-5.4
unnamed: LED-f-5.1, LED-f-6.3
unnamed: LED-f-5.6, LED-f-6.4
unnamed: LED-f-6.1, LED-g-1.3
unnamed: LED-f-6.6, LED-g-1.4
unnamed: LED-g-1.1, LED-g-2.3
unnamed: LED-g-1.6, LED-g-2.4
unnamed: LED-g-2.1, LED-g-3.3
unnamed: LED-g-2.6, LED-g-3.4
unnamed: LED-g-3.1, LED-g-4.3
unnamed: LED-g-3.6, LED-g-4.4
unnamed: LED-g-4.1, LED-g-5.3
unnamed: LED-g-4.6, LED-g-5.4
unnamed: LED-g-5.1, LED-g-6.3
unnamed: LED-g-5.6, LED-g-6.4
unnamed: LED-g-6.1, LED-h-1.3
unnamed: LED-g-6.6, LED-h-1.4
unnamed: LED-h-1.1, LED-h-2.3
unnamed: LED-h-1.6, LED-h-2.4
unnamed: LED-h-2.1, LED-h-3.3
unnamed: LED-h-2.6, LED-h-3.4
unnamed: LED-h-3.1, LED-h-4.3
unnamed: LED-h-3.6, LED-h-4.4
unnamed: LED-h-4.1, LED-h-5.3
unnamed: LED-h-4.6, LED-h-5.4
unnamed: LED-h-5.1, LED-h-6.3
unnamed: LED-h-5.6, LED-h-6.4
unnamed: LED-h-6.1, LED-i-1.3
unnamed: LED-h-6.6, LED-i-1.4
unnamed: LED-i-1.1, LED-i-2.3
unnamed: LED-i-1.6, LED-i-2.4
unnamed: LED-i-2.1, LED-i-3.3
unnamed: LED-i-2.6, LED-i-3.4
unnamed: LED-i-3.1, LED-i-4.3
unnamed: LED-i-3.6, LED-i-4.4
unnamed: LED-i-4.1, LED-i-5.3
unnamed: LED-i-4.6, LED-i-5.4
unnamed: LED-i-5.1, LED-i-6.3
unnamed: LED-i-5.6, LED-i-6.4
unnamed: LED-i-6.1, LED-j-1.3
unnamed: LED-i-6.6, LED-j-1.4
unnamed: LED-j-1.1, LED-j-2.3
unnamed: LED-j-1.6, LED-j-2.4
unnamed: LED-j-2.1, LED-j-3.3
unnamed: LED-j-2.6, LED-j-3.4
unnamed: LED-j-3.1, LED-j-4.3
unnamed: LED-j-3.6, LED-j-4.4
unnamed: LED-j-4.1, LED-j-5.3
unnamed: LED-j-4.6, LED-j-5.4
unnamed: LED-j-5.1, LED-j-6.3
unnamed: LED-j-5.6, LED-j-6.4
unnamed: LED-j-6.1, LED-k-1.3
unnamed: LED-j-6.6, LED-k-1.4
unnamed: LED-k-1.1, LED-k-2.3
unnamed: LED-k-1.6, LED-k-2.4
unnamed: LED-k-2.1, LED-k-3.3
unnamed: LED-k-2.6, LED-k-3.4
unnamed: LED-k-3.1, LED-k-4.3
unnamed: LED-k-3.6, LED-k-4.4
unnamed: LED-k-4.1, LED-k-5.3
unnamed: LED-k-4.6, LED-k-5.4
unnamed: LED-k-5.1, LED-k-6.3
unnamed: LED-k-5.6, LED-k-6.4
unnamed: LED-k-6.1, LED-l-1.3
unnamed: LED-k-6.6, LED-l-1.4
unnamed: LED-l-1.1, LED-l-2.3
unnamed: LED-l-1.6, LED-l-2.4
unnamed: LED-l-2.1, LED-l-3.3
unnamed: LED-l-2.6, LED-l-3.4
unnamed: LED-l-3.1, LED-l-4.3
unnamed: LED-l-3.6, LED-l-4.4
unnamed: LED-l-4.1, LED-l-5.3
unnamed: LED-l-4.6, LED-l-5.4
unnamed: LED-l-5.1, LED-l-6.3
unnamed: LED-l-5.6, LED-l-6.4
unnamed: LED-l-6.1, LED-m-1.3
unnamed: LED-l-6.6, LED-m-1.4
unnamed: LED-m-1.1, LED-m-2.3
unnamed: LED-m-1.6, LED-m-2.4
unnamed: LED-m-2.1, LED-m-3.3
unnamed: LED-m-2.6, LED-m-3.4
unnamed: LED-m-3.1, LED-m-4.3
unnamed: LED-m-3.6, LED-m-4.4
unnamed: LED-m-4.1, LED-m-5.3
unnamed: LED-m-4.6, LED-m-5.4
unnamed: LED-m-5.1, LED-m-6.3
unnamed: LED-m-5.6, LED-m-6.4
unnamed: LED-m-6.1, LED-n-1.3
unnamed: LED-m-6.6, LED-n-1.4
unnamed: LED-n-1.1, LED-n-2.3
unnamed: LED-n-1.6, LED-n-2.4
unnamed: LED-n-2.1, LED-n-3.3
unnamed: LED-n-2.6, LED-n-3.4
unnamed: LED-n-3.1, LED-n-4.3
unnamed: LED-n-3.6, LED-n-4.4
unnamed: LED-n-4.1, LED-n-5.3
unnamed: LED-n-4.6, LED-n-5.4
unnamed: LED-n-5.1, LED-n-6.3
unnamed: LED-n-5.6, LED-n-6.4
unnamed: LED-n-6.1, LED-o-1.3
unnamed: LED-n-6.6, LED-o-1.4
unnamed: LED-o-1.1, LED-o-2.3
unnamed: LED-o-1.6, LED-o-2.4
unnamed: LED-o-2.1, LED-o-3.3
unnamed: LED-o-2.6, LED-o-3.4
unnamed: LED-o-3.1, LED-o-4.3
unnamed: LED-o-3.6, LED-o-4.4
unnamed: LED-o-4.1, LED-o-5.3
unnamed: LED-o-4.6, LED-o-5.4
unnamed: LED-o-5.1, LED-o-6.3
unnamed: LED-o-5.6, LED-o-6.4
unnamed: LED-o-6.1, LED-p-1.3
unnamed: LED-o-6.6, LED-p-1.4
unnamed: LED-p-1.1, LED-p-2.3
unnamed: LED-p-1.6, LED-p-2.4
unnamed: LED-p-2.1, LED-p-3.3
unnamed: LED-p-2.6, LED-p-3.4
unnamed: LED-p-3.1, LED-p-4.3
unnamed: LED-p-3.6, LED-p-4.4
unnamed: LED-p-4.1, LED-p-5.3
unnamed: LED-p-4.6, LED-p-5.4
unnamed: LED-p-5.1, LED-p-6.3
unnamed: LED-p-5.6, LED-p-6.4
unnamed: LED-p-6.1, LED-q-1.3
unnamed: LED-p-6.6, LED-q-1.4
unnamed: LED-q-1.1, LED-q-2.3
unnamed: LED-q-1.6, LED-q-2.4
unnamed: LED-q-2.1, LED-q-3.3
unnamed: LED-q-2.6, LED-q-3.4
unnamed: LED-q-3.1, LED-q-4.3
unnamed: LED-q-3.6, LED-q-4.4
unnamed: LED-q-4.1, LED-q-5.3
unnamed: LED-q-4.6, LED-q-5.4
unnamed: LED-q-5.1, LED-q-6.3
unnamed: LED-q-5.6, LED-q-6.4
unnamed: LED-q-6.1, LED-r-1.3
unnamed: LED-q-6.6, LED-r-1.4
unnamed: LED-r-1.1, LED-r-2.3
unnamed: LED-r-1.6, LED-r-2.4
unnamed: LED-r-2.1, LED-r-3.3
unnamed: LED-r-2.6, LED-r-3.4
unnamed: LED-r-3.1, LED-r-4.3
unnamed: LED-r-3.6, LED-r-4.4
unnamed: LED-r-4.1, LED-r-5.3
unnamed: LED-r-4.6, LED-r-5.4
unnamed: LED-r-5.1, LED-r-6.3
unnamed: LED-r-5.6, LED-r-6.4
unnamed: LED-r-6.1, LED-s-1.3
unnamed: LED-r-6.6, LED-s-1.4
unnamed: LED-s-1.1, LED-s-2.3
unnamed: LED-s-1.6, LED-s-2.4
unnamed: LED-s-2.1, LED-s-3.3
unnamed: LED-s-2.6, LED-s-3.4
unnamed: LED-s-3.1, LED-s-4.3
unnamed: LED-s-3.6, LED-s-4.4
unnamed: LED-s-4.1, LED-s-5.3
unnamed: LED-s-4.6, LED-s-5.4
unnamed: LED-s-5.1, LED-s-6.3
unnamed: LED-s-5.6, LED-s-6.4
unnamed: LED-s-6.1, LED-t-1.3
unnamed: LED-s-6.6, LED-t-1.4
unnamed: LED-t-1.1, LED-t-2.3
unnamed: LED-t-1.6, LED-t-2.4
unnamed: LED-t-2.1, LED-t-3.3
unnamed: LED-t-2.6, LED-t-3.4
unnamed: LED-t-3.1, LED-t-4.3
unnamed: LED-t-3.6, LED-t-4.4
unnamed: LED-t-4.1, LED-t-5.3
unnamed: LED-t-4.6, LED-t-5.4
unnamed: LED-t-5.1, LED-t-6.3
unnamed: LED-t-5.6, LED-t-6.4
unnamed: LED-t-6.1, LED-u-1.3
unnamed: LED-t-6.6, LED-u-1.4
unnamed: LED-u-1.1, LED-u-2.3
unnamed: LED-u-1.6, LED-u-2.4
unnamed: LED-u-2.1, LED-u-3.3
unnamed: LED-u-2.6, LED-u-3.4
unnamed: LED-u-3.1, LED-u-4.3
unnamed: LED-u-3.6, LED-u-4.4
unnamed: LED-u-4.1, LED-u-5.3
unnamed: LED-u-4.6, LED-u-5.4
unnamed: LED-u-5.1, LED-u-6.3
unnamed: LED-u-5.6, LED-u-6.4
unnamed: LED-u-6.1, LED-v-1.3
unnamed: LED-u-6.6, LED-v-1.4
unnamed: LED-v-1.1, LED-v-2.3
unnamed: LED-v-1.6, LED-v-2.4
unnamed: LED-v-2.1, LED-v-3.3
unnamed: LED-v-2.6, LED-v-3.4
unnamed: LED-v-3.1, LED-v-4.3
unnamed: LED-v-3.6, LED-v-4.4
unnamed: LED-v-4.1, LED-v-5.3
unnamed: LED-v-4.6, LED-v-5.4
unnamed: LED-v-5.1, LED-v-6.3
unnamed: LED-v-5.6, LED-v-6.4
unnamed: LED-v-6.1, LED-w-1.3
unnamed: LED-v-6.6, LED-w-1.4
unnamed: LED-w-1.1, LED-w-2.3
unnamed: LED-w-1.6, LED-w-2.4
unnamed: LED-w-2.1, LED-w-3.3
unnamed: LED-w-2.6, LED-w-3.4
unnamed: LED-w-3.1, LED-w-4.3
unnamed: LED-w-3.6, LED-w-4.4
unnamed: LED-w-4.1, LED-w-5.3
unnamed: LED-w-4.6, LED-w-5.4
unnamed: LED-w-5.1, LED-w-6.3
unnamed: LED-w-5.6, LED-w-6.4
unnamed: R3.2, U2.44
unnamed: R4.1, U2.16
unnamed: R5.2, SW3.2
REG_1b: SW2.1, U2.26
REG_2b: SW2.2, U2.27
REG_3b: SW2.3, U2.28
REG_4b: SW2.4, U2.29
SPI1_CLK: LED-peregov-0.4, TEST6.1, U2.15
SPI1_MOSI: LED-peregov-0.3, TEST7.1, U2.17
SWITCH_MODE: D4.1, R5.1, U2.2
SYS_JTCK-SWCLK: J2.3, U2.37
SYS_JTMS-SWDIO: J2.2, U2.34
USART2_RX: J2.4, U2.13
USART2_TX: J2.5, U2.12
VDDA: C4.1, C5.1, C7.1, C8.1, C9.1, C10.1, C11.1, C12.2, D2.2, D4.2, J2.1, SW2.5, SW2.6, SW2.7, SW2.8, SW3.1, TEST2.1, U1.2, U2.1, U2.9, U2.24, U2.48
